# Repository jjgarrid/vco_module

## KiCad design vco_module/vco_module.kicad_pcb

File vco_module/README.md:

## VCO Module
Voltage controller oscilator implemented in a simple plugin module for experimentation

Based on Analog Devices HMC1163

http://analog.com/HMC1163?doc=HMC1163.pdf

FEATURES 
   * Dual output frequency range 
   * fOUT = 9.65 GHz to 10.41 GHz 
   * fOUT/2 = 4.825 GHz to 5.205 GHz 
   * Output power (POUT): 11 dBm 
   * Single-sideband (SSB) phase noise: −114 dBc/Hz at 100 kHz 

### Work in progress
    Schematics OK
    Footprints OK
    PCB        In progress

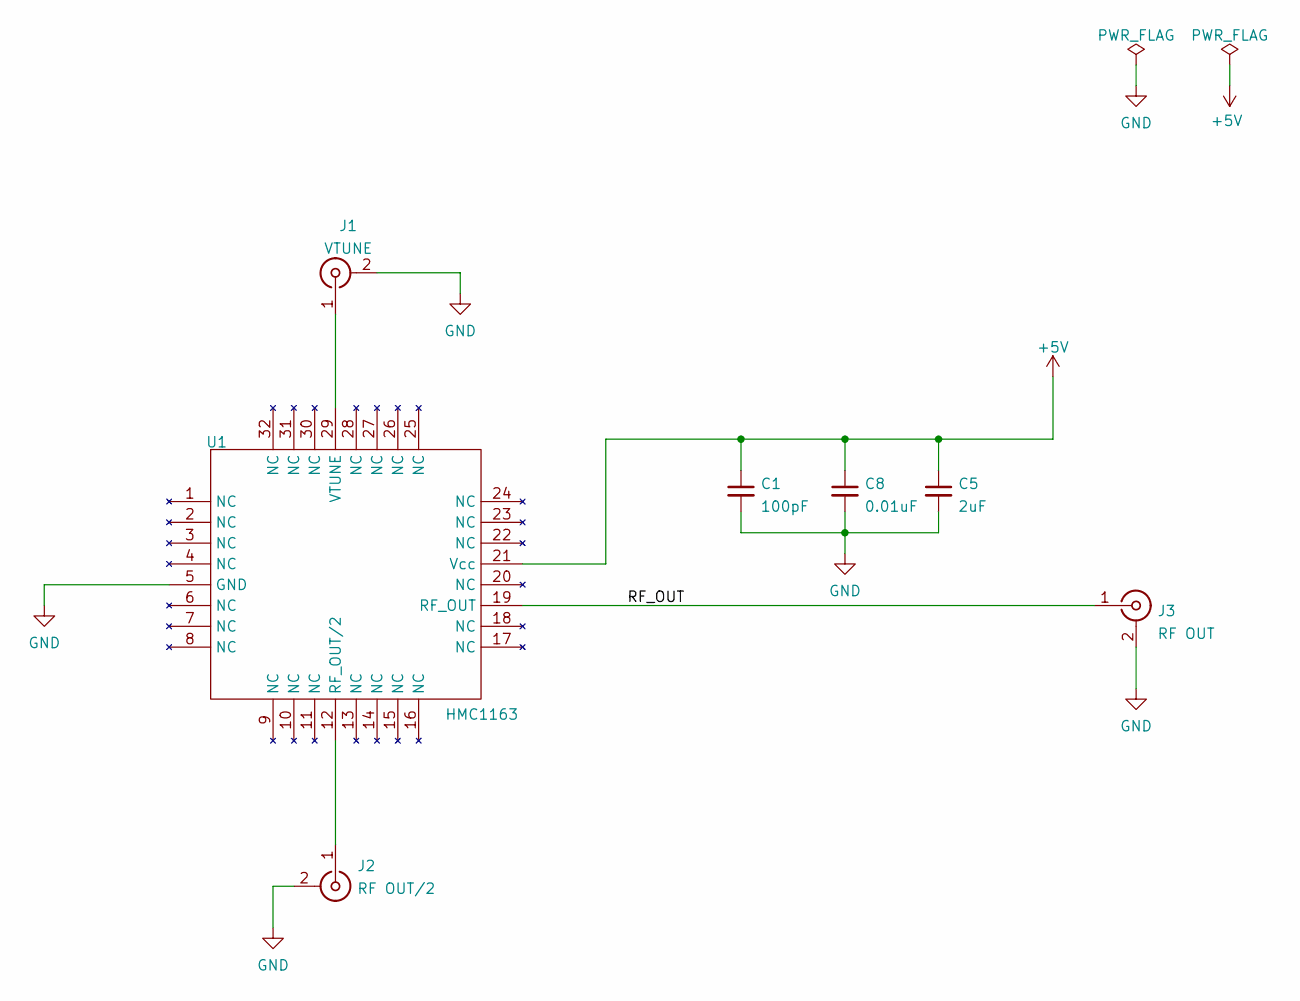
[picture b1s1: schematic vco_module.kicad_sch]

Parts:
C1: 100pF; C_0402
C5: 2uF; CP_Tantalum_Case-A_EIA-3216-18_Hand
C8: 0.01uF; C_0603
J1: VTUNE; SMA_SMD_Jack_Straight
J2: RF OUT/2; SMA_SMD_Jack_Straight
J3: RF OUT; SMA_SMD_Jack_Straight
U1: HMC1163; HMC1162LP5E

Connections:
+5V: C1.1, C5.1, C8.1, U1.21 (Vcc)
/RF_OUT: J3.1 (In), U1.19 (RF_OUT)
GND: C1.2, C5.2, C8.2, J1.2 (Ext), J2.2 (Ext), J3.2 (Ext), U1.5 (GND)
unnamed: J1.1 (In), U1.29 (VTUNE)
unnamed: J2.1 (In), U1.12 (RF_OUT/2)

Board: 2 copper layers, 7 parts (0 on the bottom side), 5 nets, no tracks yet.

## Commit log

2021-11-06 Added documentation files

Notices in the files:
parts and their libraries:
Copyright 2021 Accelerated Designs. All rights reserved.
